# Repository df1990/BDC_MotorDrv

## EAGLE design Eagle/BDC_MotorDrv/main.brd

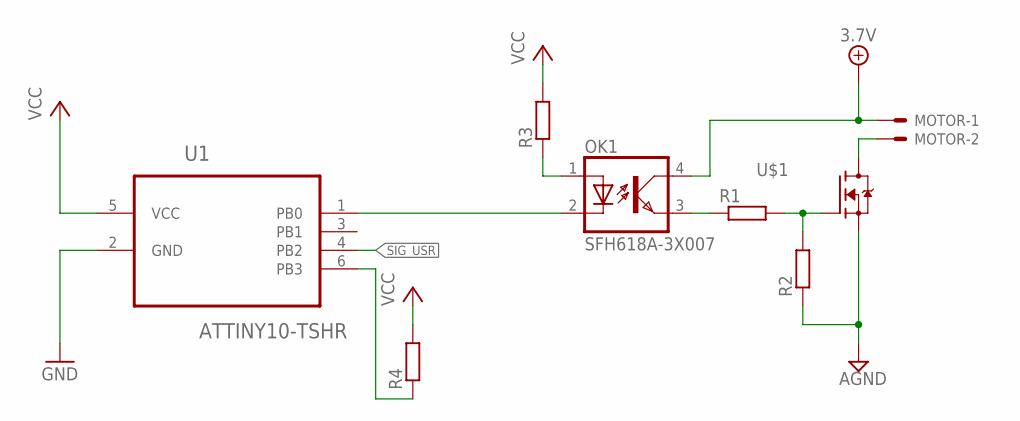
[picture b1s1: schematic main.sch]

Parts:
MOTOR: 22-23-2021
OK1: SFH618A-3X007; SMD4-7
R1, R2, R3, R4: R-EU_R0603; R0603
U1: ATTINY10-TSHR; SOT95P280X145-6N
U$1: IRLML0030; SOT23

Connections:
+12V: MOTOR.1, OK1.4 (COL)
AGND: R2.1, U$1.2 (S)
GND: U1.2 (GND)
unnamed: OK1.1 (A), R3.1
unnamed: OK1.2 (C), U1.1 (PB0)
unnamed: R1.2, R2.2, U$1.1 (G)
unnamed: MOTOR.2, U$1.3 (D)
unnamed: OK1.3 (EMIT), R1.1
unnamed: R4.1, U1.6 (PB3)
SIG_USR: U1.4 (PB2)
VCC: R3.2, R4.2, U1.5 (VCC)

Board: 2 copper layers, 8 parts (1 on the bottom side), 9 nets, no tracks yet.

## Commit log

2016-03-22 Small cosmetic changes to schematic
2016-03-23 First version of schematic finished
2016-03-23 Removed old schematic
2016-03-23 Added clean pcb
2016-04-02 Initial board setup
2016-04-02 Removed redundant power filtering
2016-04-02 Removed redundant feedback optocoupler
2016-04-02 Small cosmetic changes
